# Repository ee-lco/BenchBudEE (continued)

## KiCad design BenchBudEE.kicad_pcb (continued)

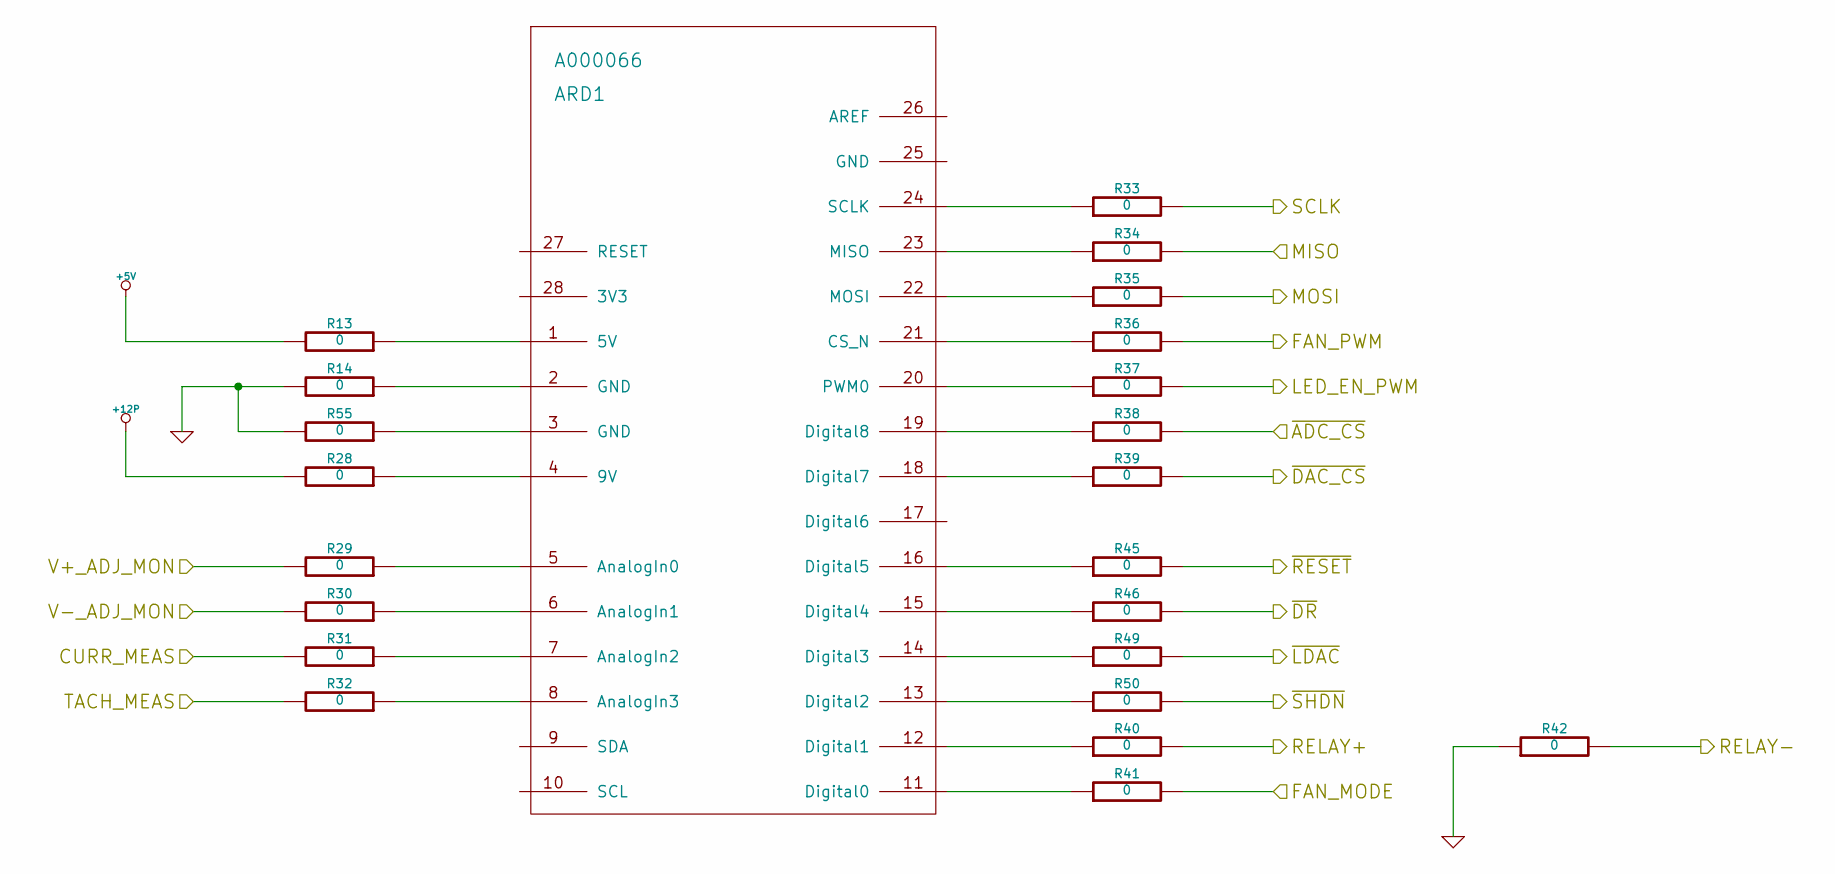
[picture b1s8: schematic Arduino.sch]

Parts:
ARD1: A000066; Arduino
R13, R14, R28, R29, R30, R31, R32, R33, R34, R35, R36, R37, R38, R39, R40, R41, R42, R45, R46, R49, R50, R55: 0; Resistor_SMD0805_Blob

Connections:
+5V: R13.2; also elsewhere on the board
+12P: R28.2; also elsewhere on the board
/Arduino/CURR_MEAS: R31.2; also elsewhere on the board
/Arduino/FAN_MODE: R41.2; also elsewhere on the board
/Arduino/FAN_PWM: R36.2; also elsewhere on the board
/Arduino/LED_EN_PWM: R37.2; also elsewhere on the board
/Arduino/MISO: R34.2; also elsewhere on the board
/Arduino/MOSI: R35.2; also elsewhere on the board
/Arduino/RELAY+: R40.2; also elsewhere on the board
/Arduino/RELAY-: R42.2; also elsewhere on the board
/Arduino/SCLK: R33.2; also elsewhere on the board
/Arduino/V+_ADJ_MON: R29.2; also elsewhere on the board
/Arduino/V-_ADJ_MON: R30.2; also elsewhere on the board
/Arduino/~ADC_CS: R38.2; also elsewhere on the board
/Arduino/~DR: R46.2; also elsewhere on the board
/Arduino/~LDAC: R49.2; also elsewhere on the board
/Arduino/~RESET: R45.2; also elsewhere on the board
/Arduino/~SHDN: R50.2; also elsewhere on the board
/Fan/CS_N: R39.2; also elsewhere on the board
/Fan/TACH_IN: R32.2; also elsewhere on the board
GND: R14.2, R42.1, R55.2; also elsewhere on the board
unnamed: ARD1.1 (5V), R13.1
unnamed: ARD1.2 (GND), R14.1
unnamed: ARD1.3 (GND), R55.1
unnamed: ARD1.4 (9V), R28.1
unnamed: ARD1.5 (AnalogIn0), R29.1
unnamed: ARD1.6 (AnalogIn1), R30.1
unnamed: ARD1.7 (AnalogIn2), R31.1
unnamed: ARD1.8 (AnalogIn3), R32.1
unnamed: ARD1.11 (Digital0), R41.1
unnamed: ARD1.12 (Digital1), R40.1
unnamed: ARD1.13 (Digital2), R50.1
unnamed: ARD1.14 (Digital3), R49.1
unnamed: ARD1.15 (Digital4), R46.1
unnamed: ARD1.16 (Digital5), R45.1
unnamed: ARD1.18 (Digital7), R39.1
unnamed: ARD1.19 (Digital8), R38.1
unnamed: ARD1.20 (PWM0), R37.1
unnamed: ARD1.21 (CS_N), R36.1
unnamed: ARD1.22 (MOSI), R35.1
unnamed: ARD1.23 (MISO), R34.1
unnamed: ARD1.24 (SCLK), R33.1

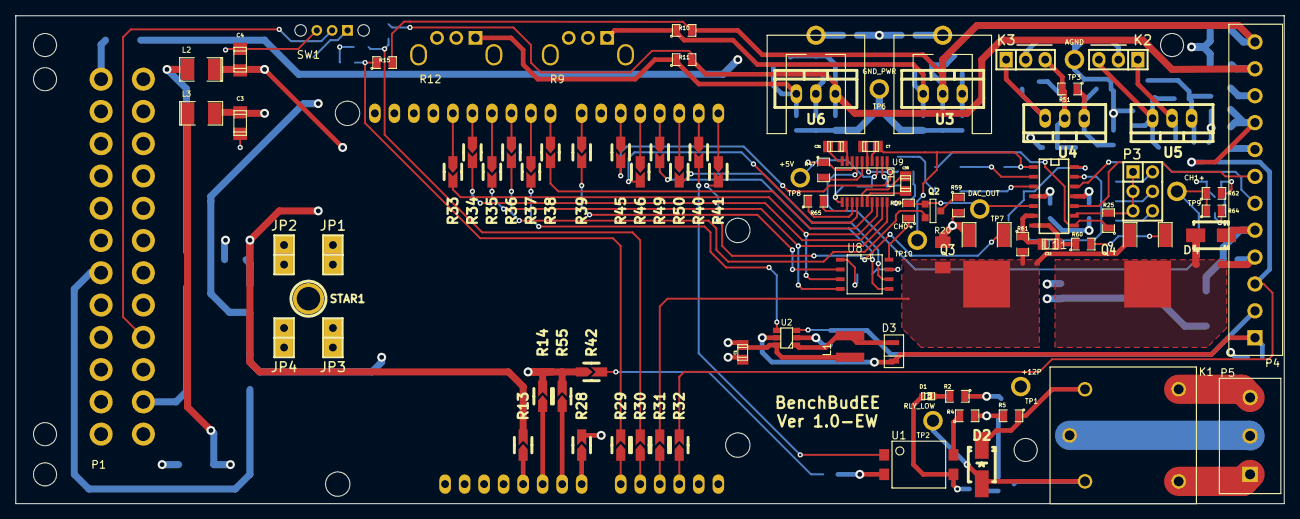
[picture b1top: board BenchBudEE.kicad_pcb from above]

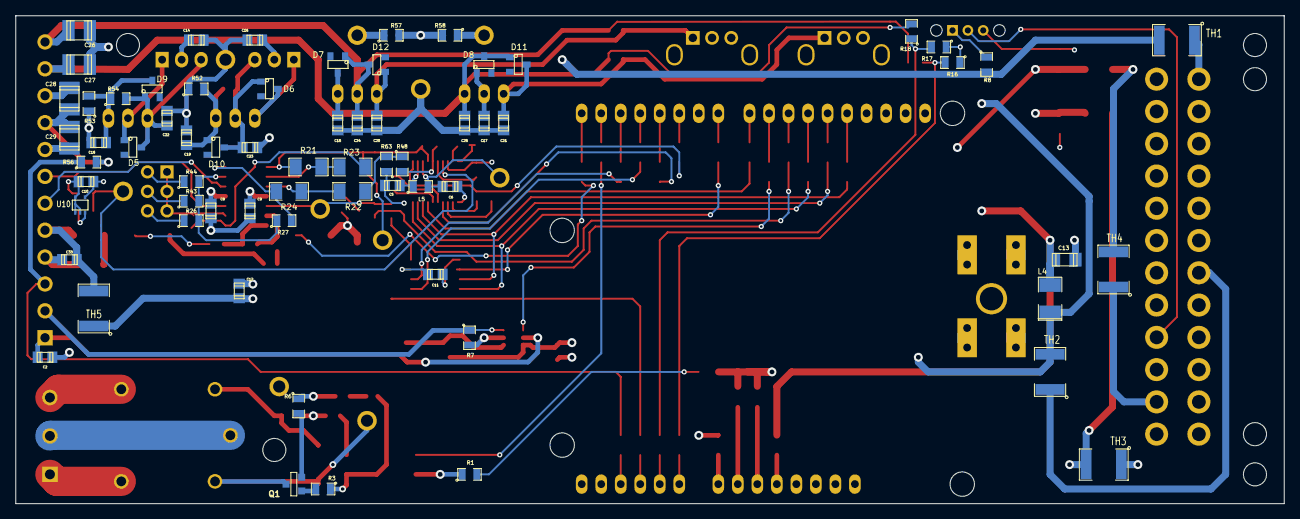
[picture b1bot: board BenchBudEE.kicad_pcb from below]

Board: 4 copper layers, 165.1 x 63.5 mm, 162 parts (67 on the bottom side), 115 nets.

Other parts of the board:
3 mm, 3 mm#2, 3 mm#3, 3 mm#4: VAL**; 3mm-NPTH

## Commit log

2014-01-30 Created empty BenchBudEE KiCad project
2014-01-30 Created schematic hierarchy
2014-02-03 Inputs/outputs added to hierarchical schematics
2014-02-03 Rough schematic created for thermocouple circuit
2014-02-03 Rough schematic created for fan driver circuit
2014-02-04 Added BenchBudEE.lib and symbol for SPDT relay
2014-02-04 Rough schematic created for relay circuit
2014-02-04 -12P power symbol added
2014-02-04 Rough schematic created for power protection and filtering circuit
2014-02-04 Power protection and filtering sheet added to schematic
2014-02-04 12volt net name fixed on relay schematic: use +12P instead of +12V
2014-02-05 Power protection and filtering circuit moved to Power.sch, was accidentally on PowerAdjustmentMonitor.sch
2014-02-05 Front-end V+ and V- power symbols added
2014-02-05 Rough schematic created for power control, conditioning and monitoring circuit
2014-02-05 Updated top level input/outputs
2014-02-05 Added symbol for AP5726 LED driver
2014-02-05 Rough schematic created for LED driver circuit
2014-02-12 Added Arduino and top-level connections
2014-02-12 Current/fan driver circuit reworked
2014-02-12 Some cleanup/fixes on the top-level
2014-02-16 Basic PCB setup done and changed some preferences
2014-02-18 Added footprints for the relay module, preliminarily annotated schematic, relay components placed on PCB
2014-02-19 Added component association file BenchBudEE.cmp
2014-02-19 Associated and placed the thermocouple module
2014-02-22 Associated and placed the terminal blocks and ATX header
2014-02-22 Associated and placed the Arduino
2014-02-23 Associated and placed the Current/Fan Driver Module
2014-02-23 Associated and placed the Power Filter Module
2014-02-23 Associated and placed the Power Modification Module
2014-02-23 Associated and placed the LED Driver Module
2014-02-23 Rearranged layout a bit and added heatsinks
2014-03-03 Various minor updates after Ground and Power Planes video
2014-03-03 Updates from Reality Check video
2014-03-03 Updates from Layout Work Session 2 video and KiCAD update
2014-03-03 Updates from Layout Work Session 3 video
2014-03-04 Updates from Layout Work Session 4 video
2014-03-04 Updates from Layout Work Session 5 video
2014-03-04 Updates from Layout Work Session 6 video
2014-03-04 Updates from Layout Work Session 7 video
2014-03-05 Updates from Connecting Ground Planes video
2014-03-08 Relay layout
2014-03-08 Power output layout
2014-03-08 LED Module layout
2014-03-11 Fan and TC module layout
2014-03-11 Arduino layout
2014-03-11 Connected remaing nets
2014-03-12 Connected remaining ADC pins, some silk screen updates
2014-03-12 More silk screen tweaks
2014-03-12 More small tweaks (cf. Layout Work Session 16)
2014-03-14 Test points added, silk screen updates
2014-03-14 Added some R/C to analog sections
2014-03-15 Via annular ring size fixed
2014-03-15 Ground point tweaked a bit
2014-04-18 Assigned values to passives in Arduino, power adjustment monitor, relay and terminal block schematics
2014-04-18 BOM added
2014-04-18 BOM: found a replacement for the AP5726
2014-04-18 Assigned values to passives in fan and thermocouple schematics
2014-04-19 Back-annotated footprints into the schematic
2014-04-19 BOM updated
2014-04-20 Final part numbers added to schematic, cross-checked KiCAD BOM against manual BOM
2014-04-20 Tweak some quantities on the BOM, 100K and 1M resistors added
2014-04-21 Updated BOM for Farnell order
2014-04-21 Updated BOM for second Farnell order
